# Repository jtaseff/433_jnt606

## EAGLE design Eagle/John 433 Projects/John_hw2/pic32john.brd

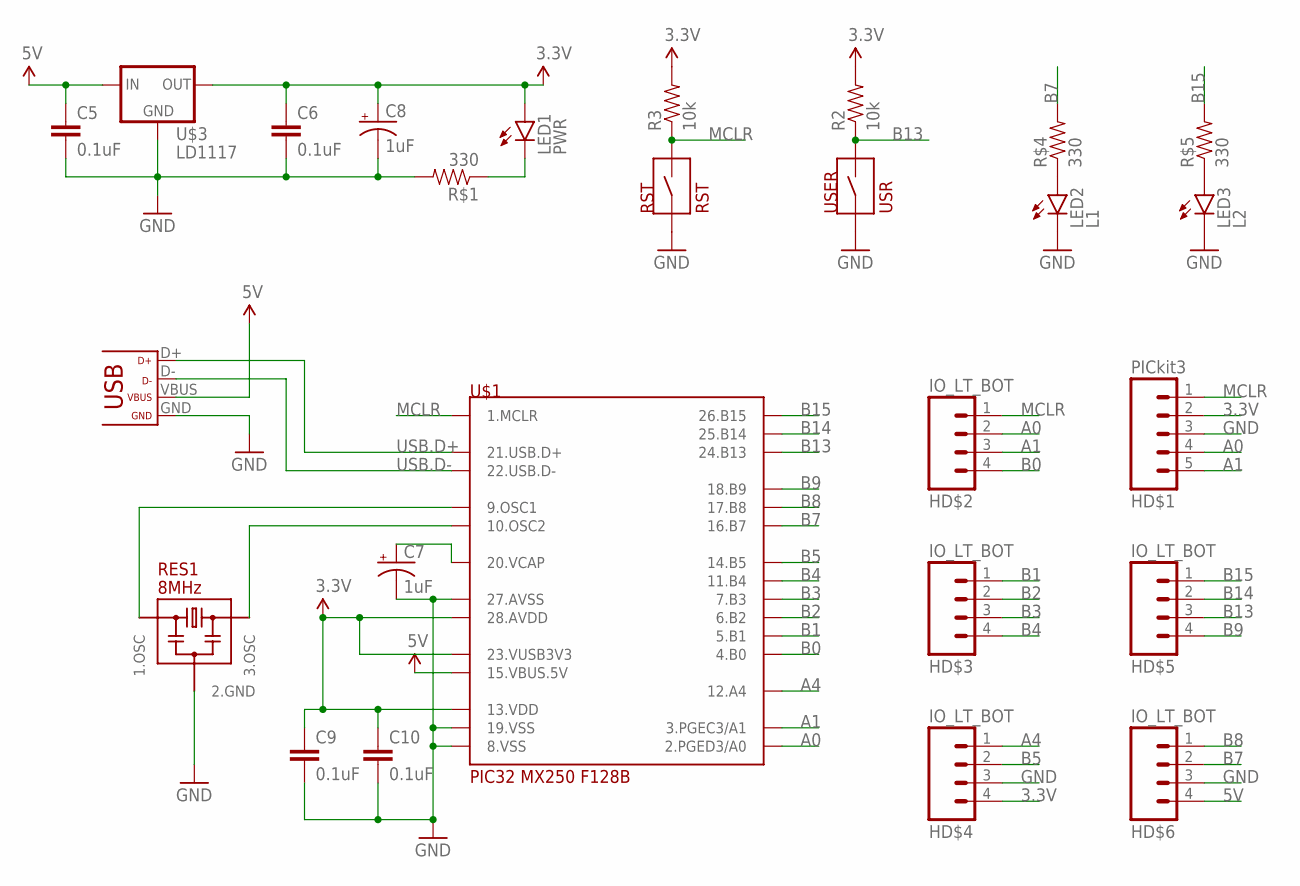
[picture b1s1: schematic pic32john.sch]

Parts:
C5, C6, C9, C10: 0.1uF; CAP-PTH-SMALL
C7, C8: 1uF; CPOL-RADIAL-10UF-25V
HD$1: PICkit3; 1X05
HD$2, HD$3, HD$4, HD$5, HD$6: IO_LT_BOT; 1X04
LED1: PWR; LED3MM
LED2: L1; LED3MM
LED3: L2; LED3MM
R2, R3: 10k; AXIAL-0.4
R$1, R$4, R$5: 330; AXIAL-0.4
RES1: 8MHz; RESONATOR_PTH
RST: RST; BTN_P8072
U$1: PIC32MX250F128B; DIL_28_3_JOHN
U$2: USB; USB-MINIB
U$3: LD1117; TO220
USER: USR; BTN_P8072

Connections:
3.3V: C6.1, C8.1 (+), C9.1, C10.1, HD$1.2, HD$4.4, LED1.A, R2.P$2 (2), R3.P$2 (2), U$1.P$13 (13.VDD), U$1.P$23 (23.VUSB3V3), U$1.P$28 (28.AVDD), U$3.2 (OUT)
5V: C5.1, HD$6.4, U$1.P$15 (15.VBUS.5V), U$2.VBUS, U$3.3 (IN)
A0: HD$1.4, HD$2.2, U$1.P$2 (2.PGED3/A0)
A1: HD$1.5, HD$2.3, U$1.P$3 (3.PGEC3/A1)
A4: HD$4.1, U$1.P$12 (12.A4)
B0: HD$2.4, U$1.P$4 (4.B0)
B1: HD$3.1, U$1.P$5 (5.B1)
B2: HD$3.2, U$1.P$6 (6.B2)
B3: HD$3.3, U$1.P$7 (7.B3)
B4: HD$3.4, U$1.P$11 (11.B4)
B5: HD$4.2, U$1.P$14 (14.B5)
B7: HD$6.2, R$4.P$2 (2), U$1.P$16 (16.B7)
B8: HD$6.1, U$1.P$17 (17.B8)
B9: HD$5.4, U$1.P$18 (18.B9)
B13: HD$5.3, R2.P$1 (1), U$1.P$24 (24.B13), USER.P$2
B14: HD$5.2, U$1.P$25 (25.B14)
B15: HD$5.1, R$5.P$2 (2), U$1.P$26 (26.B15)
GND: C5.2, C6.2, C7.2 (-), C8.2 (-), C9.2, C10.2, HD$1.3, HD$4.3, HD$6.3, LED2.K (C), LED3.K (C), R$1.P$2 (2), RES1.P$2 (2.GND), RST.P$1, U$1.P$8 (8.VSS), U$1.P$19 (19.VSS), U$1.P$27 (27.AVSS), U$2.GND, U$3.1 (GND), USER.P$1
MCLR: HD$1.1, HD$2.1, R3.P$1 (1), RST.P$2, U$1.P$1 (1.MCLR)
unnamed: RES1.P$3 (1.OSC), U$1.P$9 (9.OSC1)
unnamed: RES1.P$1 (3.OSC), U$1.P$10 (10.OSC2)
unnamed: LED1.K (C), R$1.P$1 (1)
unnamed: LED2.A, R$4.P$1 (1)
unnamed: C7.1 (+), U$1.P$20 (20.VCAP)
unnamed: LED3.A, R$5.P$1 (1)
USB.D+: U$1.P$21 (21.USB.D+), U$2.D+
USB.D-: U$1.P$22 (22.USB.D-), U$2.D-

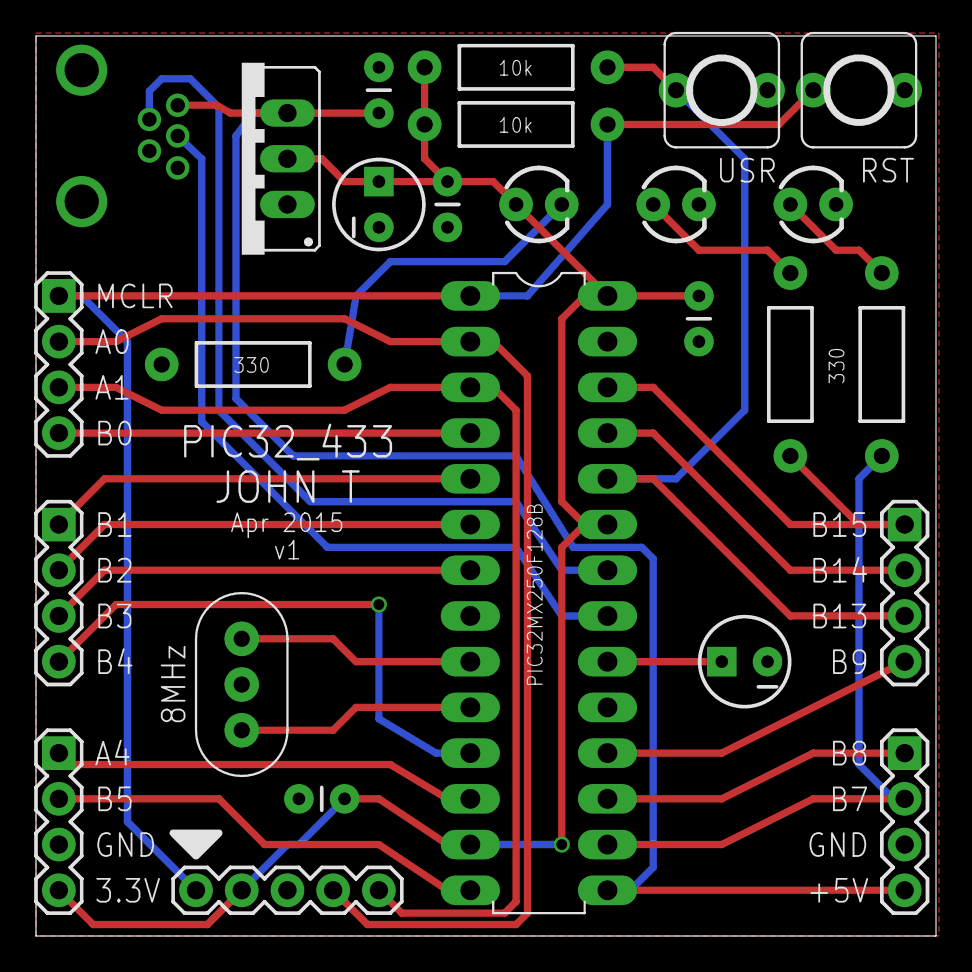
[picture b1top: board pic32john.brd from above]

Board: 2 copper layers, 50.0 x 50.0 mm, 26 parts (0 on the bottom side), 27 nets.

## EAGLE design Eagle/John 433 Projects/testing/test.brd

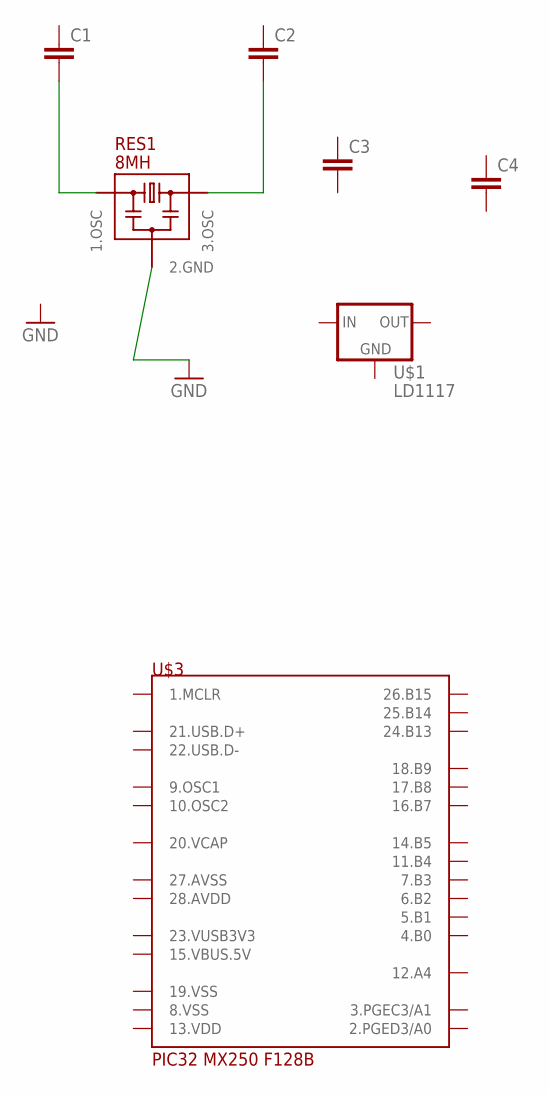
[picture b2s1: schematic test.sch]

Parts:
C1, C2, C3: CAPPTH1; CAP-PTH-5MM
C4: CAPPTH; CAP-PTH-SMALL
RES1: 8MH; RESONATOR_PTH
U$1: LD1117; TO220
U$3: PIC32MX250F128B; DIL_28_3_JOHN

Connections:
8.VSS: U$3.P$8 (8.VSS)
13.VDD: U$3.P$13 (13.VDD)
15.VBUS.5V: U$3.P$15 (15.VBUS.5V)
19.VSS: U$3.P$19 (19.VSS)
20.VCAP: U$3.P$20 (20.VCAP)
23.VUSB3V3: U$3.P$23 (23.VUSB3V3)
27.AVSS: U$3.P$27 (27.AVSS)
28.AVDD: U$3.P$28 (28.AVDD)
GND: RES1.P$2 (2.GND)
unnamed: C1.2, RES1.P$3 (1.OSC)
unnamed: C2.2, RES1.P$1 (3.OSC)

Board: 2 copper layers, 7 parts (0 on the bottom side), 2 nets, no tracks yet.

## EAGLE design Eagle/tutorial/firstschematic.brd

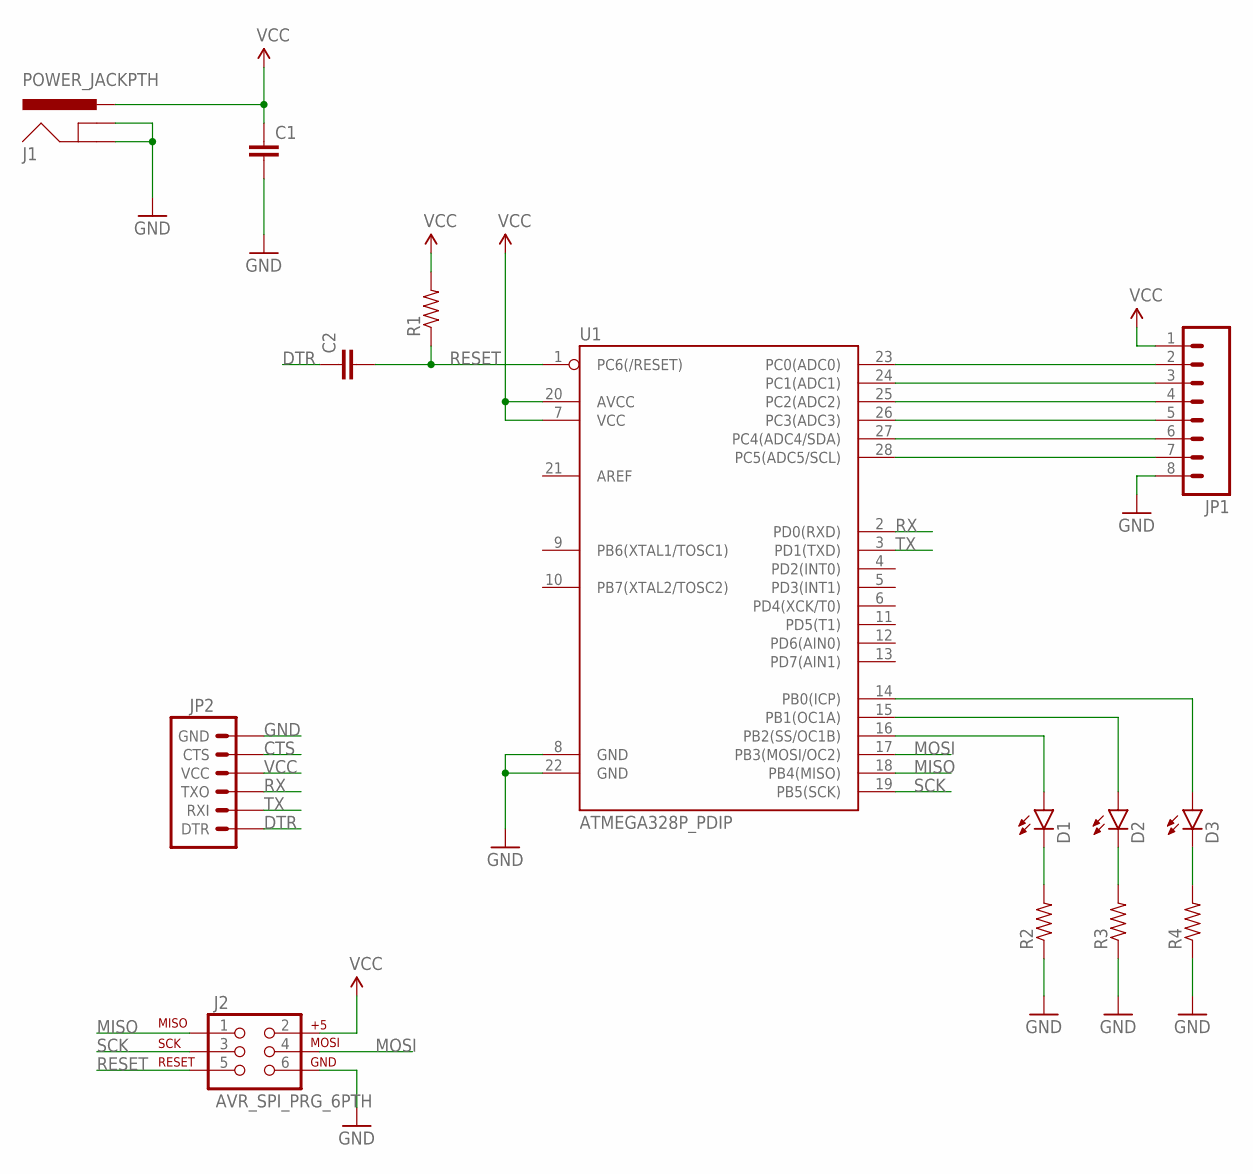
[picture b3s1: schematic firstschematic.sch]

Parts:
C1, C2: CAPPTH; CAP-PTH-SMALL
D1, D2, D3: LED5MM
J1: POWER_JACKPTH; POWER_JACK_PTH
J2: AVR_SPI_PRG_6PTH; 2X3
JP1: M08; 1X08_ROUND
JP2: ARDUINO_SERIAL_PROGRAMPTH; 1X06
R1, R2, R3, R4: RESISTORPTH-1/4W; AXIAL-0.4
U1: ATMEGA328P_PDIP; DIL28-3

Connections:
CTS: JP2.5 (CTS)
DTR: C2.1, JP2.1 (DTR)
GND: C1.2, J1.GND, J1.GNDBREAK, J2.6, JP1.8, JP2.6 (GND), R2.P$1 (1), R3.P$1 (1), R4.P$1 (1), U1.8 (GND), U1.22 (GND)
MISO: J2.1, U1.18 (PB4(MISO))
MOSI: J2.4, U1.17 (PB3(MOSI/OC2))
unnamed: D1.K (C), R2.P$2 (2)
unnamed: D3.A, U1.14 (PB0(ICP))
unnamed: D2.A, U1.15 (PB1(OC1A))
unnamed: D1.A, U1.16 (PB2(SS/OC1B))
unnamed: D2.K (C), R3.P$2 (2)
unnamed: D3.K (C), R4.P$2 (2)
unnamed: JP1.2, U1.23 (PC0(ADC0))
unnamed: JP1.3, U1.24 (PC1(ADC1))
unnamed: JP1.4, U1.25 (PC2(ADC2))
unnamed: JP1.5, U1.26 (PC3(ADC3))
unnamed: JP1.6, U1.27 (PC4(ADC4/SDA))
unnamed: JP1.7, U1.28 (PC5(ADC5/SCL))
RESET: C2.2, J2.5, R1.P$1 (1), U1.1 (PC6(/RESET))
RX: JP2.3 (TXO), U1.2 (PD0(RXD))
SCK: J2.3, U1.19 (PB5(SCK))
TX: JP2.2 (RXI), U1.3 (PD1(TXD))
VCC: C1.1, J1.PWR, J2.2, JP1.1, JP2.4 (VCC), R1.P$2 (2), U1.7 (VCC), U1.20 (AVCC)

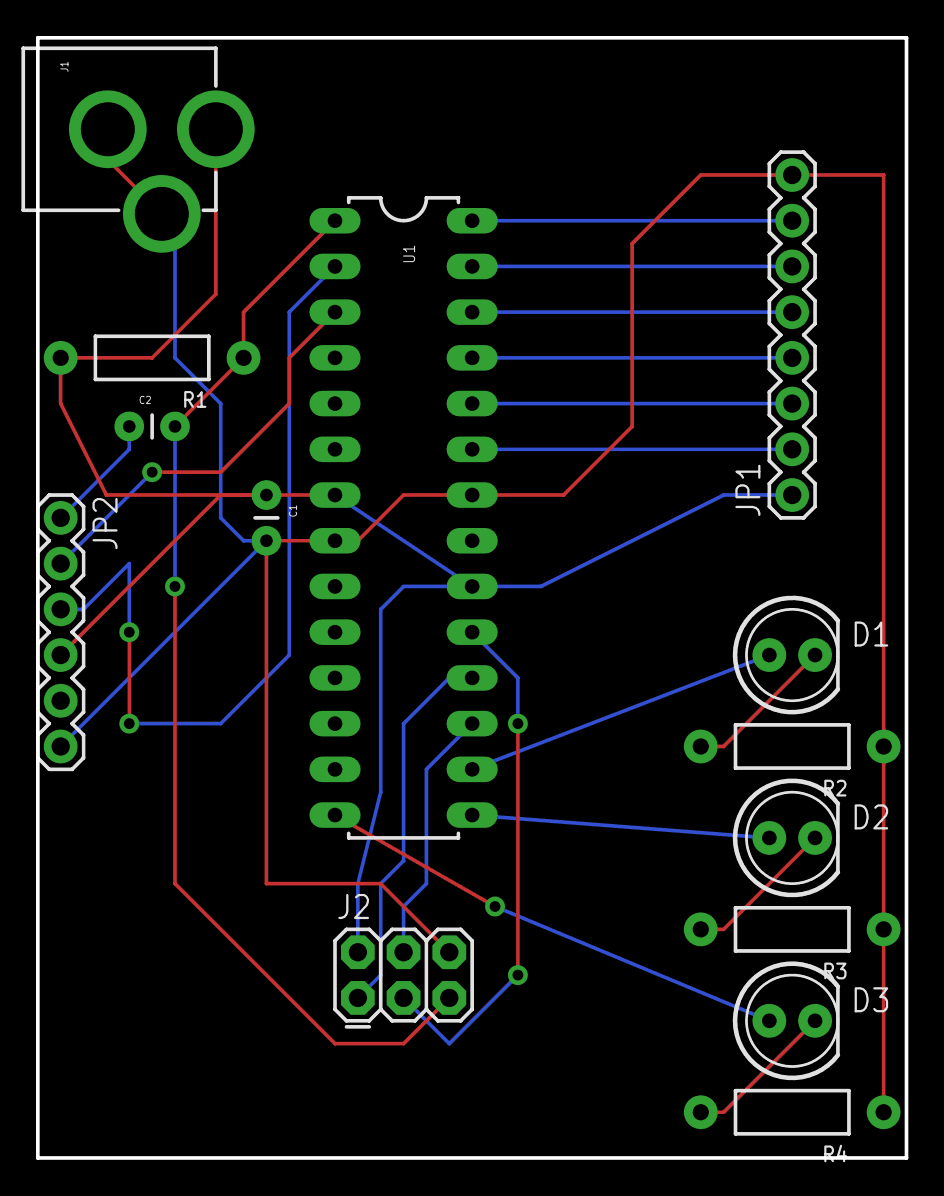
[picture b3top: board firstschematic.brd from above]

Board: 2 copper layers, 48.3 x 62.2 mm, 14 parts (0 on the bottom side), 21 nets.

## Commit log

2015-04-01 :circus_tent: Added .gitattributes & .gitignore files
2015-04-01 empty project hw1
2015-04-02 HW1 completed upload
2015-04-04 testing servo pwm
2015-04-04 eagle tutorial
2015-04-04 reorganize
2015-04-04 reorg v2
2015-04-05 schematic first version
2015-04-05 board unrouted
2015-04-05 layout mod unrouted
2015-04-05 done draft of board
2015-04-05 first draft small changes
2015-04-05 draft 1 done and labelled
2015-04-09 board cam finished
2015-04-12 oled finally working
2015-04-13 starting graphics lib
2015-04-14 text drawing working
2015-04-14 more graphics lib working
2015-04-14 hw4 submit pic
2015-04-14 fill and inverted text
2015-04-16 hw5 finished
2015-04-18 organizing
2015-04-23 hw6 push
    blinky LED harmony project
2015-04-24 HW7 first push, default project working
2015-04-25 HW7 completed accelerometer mouse
2015-04-29 reorganizing code library
    common files for accel, OLED, graphics
2015-04-29 hid_basic
    compiling with oled and accel working
2015-04-29 hid_basic
    custom data is transferring
2015-04-29 hid_basic
    finally able to send string to screen
2015-04-29 hid_basic
    moved hidapi into git for version history
2015-04-30 hid_basic
    copied backup of working draft to git
2015-04-30 hid_basic
    got an accelerometer data parsed
2015-04-30 hid done
2015-04-30 wheel cad
2015-05-18 HW9 wheel and box finished
2015-05-19 started android, hello world
2015-05-19 robot v1 lasercut
2015-05-22 sample camera app test
2015-05-24 camera app - my own
2015-05-26 more camera and USB testing
2015-06-01 USB CDC working!
2015-06-03 trying to detect being lost/camera washing out
2015-06-04 final robot code hw16

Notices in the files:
parts and their libraries:
SparkFun-Capacitors: Licensing: Creative Commons ShareAlike 4.0 International - https://creativecommons.org/licenses/by-sa/4.0
